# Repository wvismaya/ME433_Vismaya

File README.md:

Please refer the [Wiki here.](https://github.com/wvismaya/Northwestern_MSME_2k1617/wiki/Home)

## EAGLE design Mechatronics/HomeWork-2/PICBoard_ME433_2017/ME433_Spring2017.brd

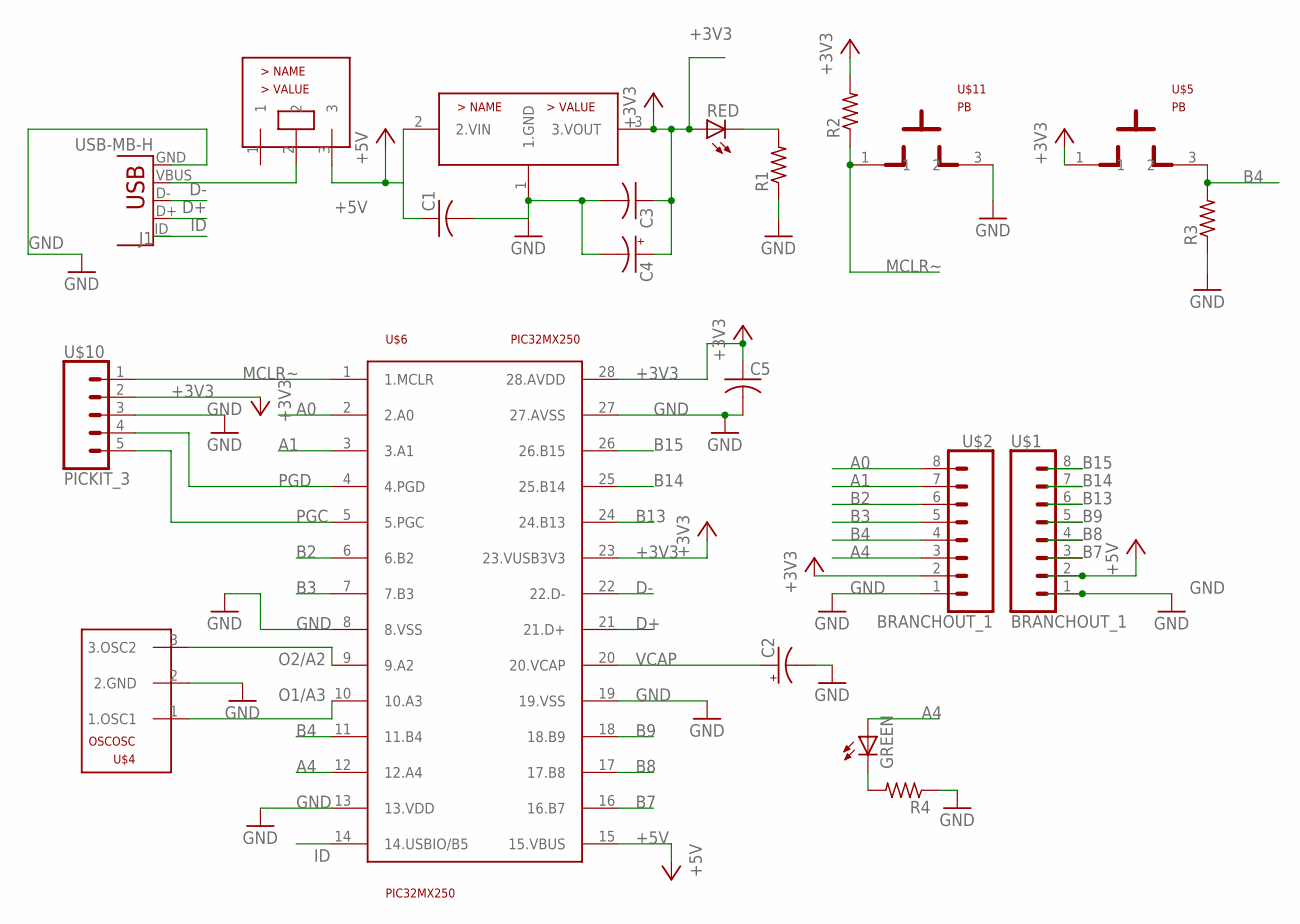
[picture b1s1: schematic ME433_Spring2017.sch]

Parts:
C1, C3, C5: C-US025-025X050; C025-025X050
C2, C4: CPOL-USB45181B; B45181B
GREEN: LED3MM
J1: USB-MB-H
R1, R2, R3, R4: R-US_0204/7; 0204/7
RED: LED3MM
U$1, U$2: BRANCHOUT_1; 1X08
U$4: OSCOSC; OSC
U$5, U$11: PB
U$6: PIC32MX250; DIL28-3
U$8: SLIDE
U$10: PICKIT_3; 1X05
_: MCP1702; TO92

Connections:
+3V3: C3.1, C4.+, C5.1, R2.2, RED.A, U$2.2, U$5.1, U$6.23 (23.VUSB3V3), U$6.28 (28.AVDD), U$10.2 (2.VDD), _.3 (3.VOUT)
+5V: C1.1, U$1.2, U$6.15 (15.VBUS), U$8.3, _.2 (2.VIN)
A0: U$2.8, U$6.2 (2.A0)
A1: U$2.7, U$6.3 (3.A1)
A4: GREEN.A, U$2.3, U$6.12 (12.A4)
B2: U$2.6, U$6.6 (6.B2)
B3: U$2.5, U$6.7 (7.B3)
B4: R3.2, U$2.4, U$5.3 (2), U$6.11 (11.B4)
B7: U$1.3, U$6.16 (16.B7)
B8: U$1.4, U$6.17 (17.B8)
B9: U$1.5, U$6.18 (18.B9)
B13: U$1.6, U$6.24 (24.B13)
B14: U$1.7, U$6.25 (25.B14)
B15: U$1.8, U$6.26 (26.B15)
D+: J1.D+, U$6.21 (21.D+)
D-: J1.D-, U$6.22 (22.D-)
GND: C1.2, C2.-, C3.2, C4.-, C5.2, J1.GND, R1.1, R3.1, R4.1, U$1.1, U$2.1, U$4.2 (2.GND), U$6.8 (8.VSS), U$6.13 (13.VDD), U$6.19 (19.VSS), U$6.27 (27.AVSS), U$10.3 (3.VSS), U$11.3 (2), _.1 (1.GND)
ID: J1.ID, U$6.14 (14.USBIO/B5)
MCLR~: R2.1, U$6.1 (1.MCLR), U$10.1 (1.MCLR~), U$11.1
unnamed: J1.VBUS, U$8.2
unnamed: R1.2, RED.K (C)
unnamed: GREEN.K (C), R4.2
O1/A3: U$4.1 (1.OSC1), U$6.10 (10.A3)
O2/A2: U$4.3 (3.OSC2), U$6.9 (9.A2)
PGC: U$6.5 (5.PGC), U$10.5 (5.PGC)
PGD: U$6.4 (4.PGD), U$10.4 (4.PGD)
VCAP: C2.+, U$6.20 (20.VCAP)

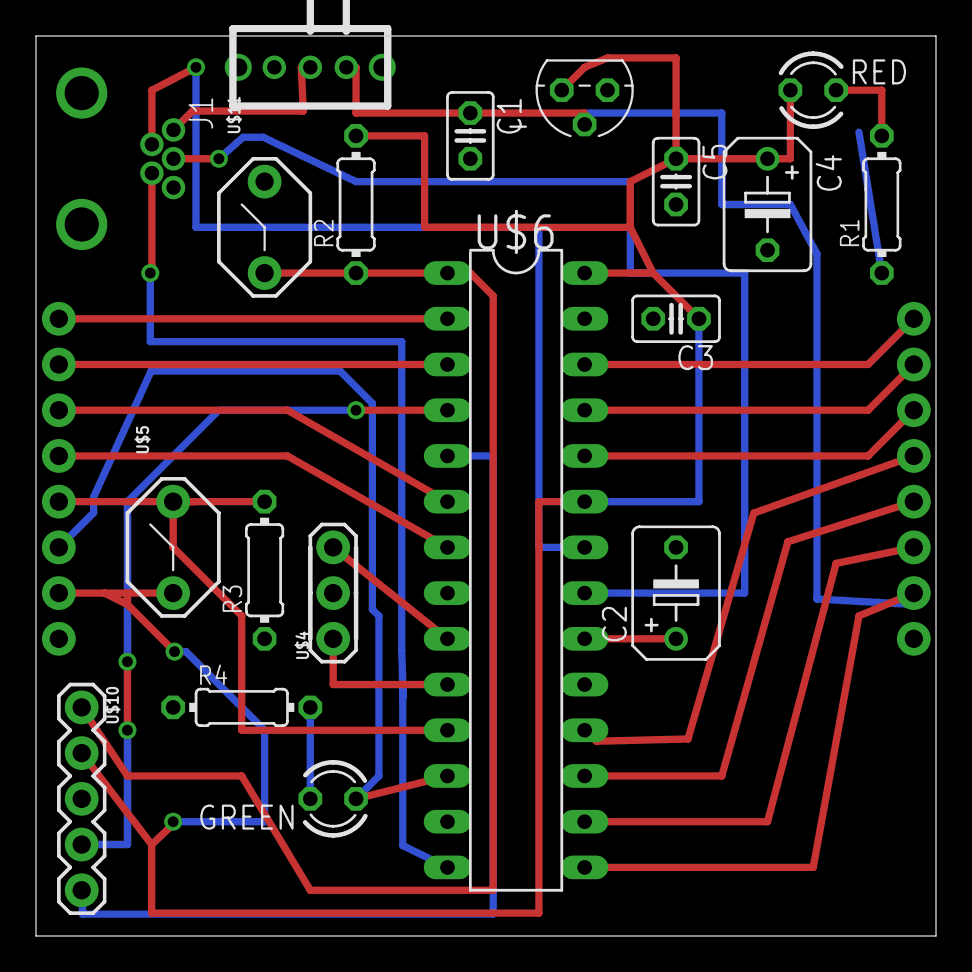
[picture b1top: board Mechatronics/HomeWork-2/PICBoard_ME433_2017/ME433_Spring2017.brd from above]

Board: 2 copper layers, 50.0 x 50.0 mm, 21 parts (0 on the bottom side), 27 nets.

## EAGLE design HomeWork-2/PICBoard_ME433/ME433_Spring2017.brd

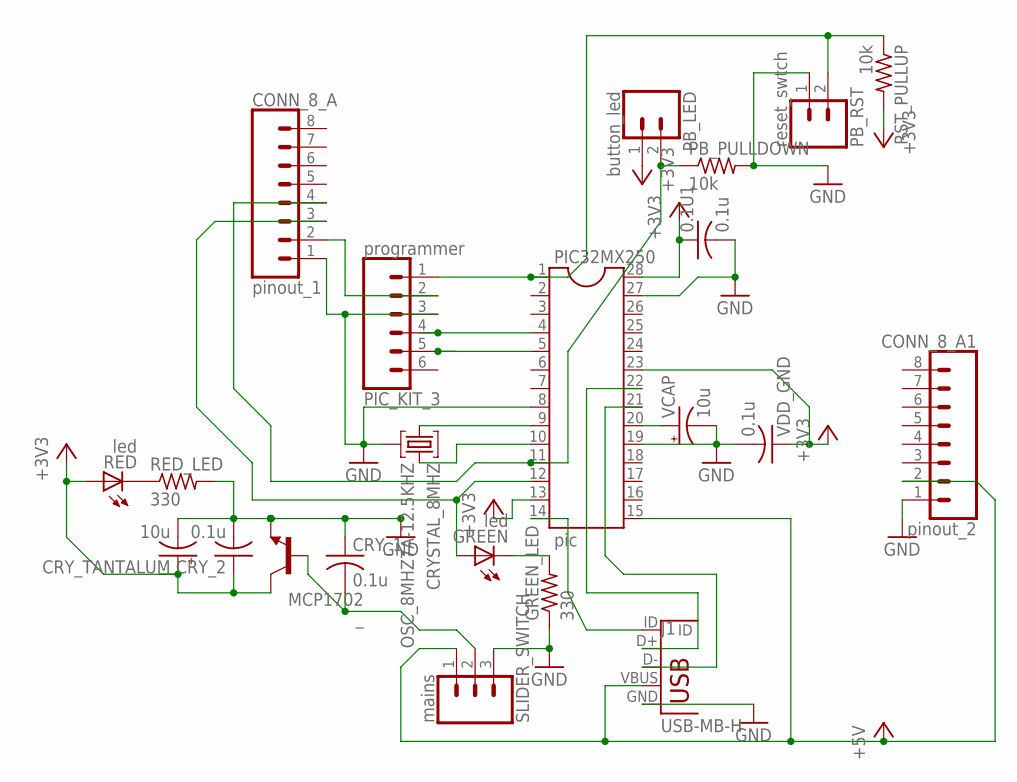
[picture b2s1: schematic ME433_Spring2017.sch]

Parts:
0.1U1: 0.1u; C025-025X050
CONN_8_A: pinout_1; 1X08
CONN_8_A1: pinout_2; 1X08
CRYSTAL_8MHZ: OSC_8MHZ7A-12.5KHZ; HC49U
CRY_1, CRY_2: 0.1u; C025-025X050
CRY_TANTALUM: 10u; B45181B
GREEN: led; SFH482
GREEN_LED: 330; 0204/7
J1: USB-MB-H
PB_LED: button_led; BUTTONS
PB_PULLDOWN: 10k; 0204/7
PB_RST: reset_swtch; BUTTONS
PIC32MX250: pic; PIC
PIC_KIT_3: programmer; 1X06_NO_SILK
RED: led; SFH482
RED_LED: 330; 0204/7
RST_PULLUP: 10k; 0204/7
SLIDER_SWITCH: mains; SLIDER_SWITCH_1MM
VCAP: 10u; B45181B
VDD_GND: 0.1u; C025-025X050
_: MCP1702

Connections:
+3V3: 0.1U1.1, CRY_2.1, CRY_TANTALUM.+, PB_LED.1, PIC32MX250.13, PIC32MX250.23, PIC32MX250.28, RED.A, RST_PULLUP.2, VDD_GND.1, _.C
+5V: CONN_8_A1.2, J1.VBUS, PIC32MX250.15, SLIDER_SWITCH.1
GND: 0.1U1.2, CONN_8_A.1, CONN_8_A1.1, CRYSTAL_8MHZ.2, CRY_1.1, CRY_2.2, CRY_TANTALUM.-, GREEN_LED.1, J1.GND, PB_PULLDOWN.2, PB_RST.1, PIC32MX250.8, PIC32MX250.19, PIC32MX250.27, PIC_KIT_3.3, RED_LED.2, SLIDER_SWITCH.3, VCAP.-, VDD_GND.2, _.E
unnamed: CONN_8_A.2, PIC_KIT_3.2
unnamed: PIC32MX250.4, PIC_KIT_3.4
unnamed: CONN_8_A.3, GREEN.A, PIC32MX250.12
unnamed: J1.D+, PIC32MX250.22
unnamed: CRYSTAL_8MHZ.1, PIC32MX250.9
unnamed: CRYSTAL_8MHZ.3, PIC32MX250.10
unnamed: GREEN.K (C), GREEN_LED.2
unnamed: PIC32MX250.5, PIC_KIT_3.5
unnamed: J1.D-, PIC32MX250.21
unnamed: CONN_8_A.4, PB_LED.2, PB_PULLDOWN.1, PIC32MX250.11
unnamed: PIC32MX250.20, VCAP.+
unnamed: CRY_1.2, SLIDER_SWITCH.2, _.B
unnamed: PB_RST.2, PIC32MX250.1, PIC_KIT_3.1, RST_PULLUP.1
unnamed: RED.K (C), RED_LED.1
unnamed: J1.ID, PIC32MX250.14

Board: 2 copper layers, 22 parts (1 on the bottom side), 18 nets, no tracks yet.

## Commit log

2017-03-30 Circuit Diagram of seemingly working prototype
2017-03-30 Uploaded without making a folder
2017-03-30 Upload of circuit diagram 1.1
2017-03-30 Screenshots of Clean-Unclean power supply
2017-03-30 Version1.1: Button=push-blinky
2017-03-30 1KHz Square wave
2017-03-30 Core Timer Added for Delays
2017-03-30 Macros Values perfected
2017-03-30 Circuit-Breadboard Snapshot
2017-03-30 Submission Ready
2017-04-02 Initialized new library
2017-04-02 Library Version #1; Initialize the Schematic
2017-04-02 Schematic Version #1
2017-04-02 Schematic Version #2
2017-04-04 Schematic Version #3 - Added PTH USB package
2017-04-04 Change in Schematic #1
2017-04-04 Final Layout #1
2017-04-05 Final Layout draft#2: Parse error for DRC
2017-04-07 Final Board
2017-04-07 Zip File: Submission Ready
2017-04-11 Update in main code
2017-04-11 Adding the Schematic: EAGLE
2017-04-11 Quick Reference picture of Schematic
2017-04-11 Main SPI code
2017-04-11 Display output
2017-04-11 SPI: Seperating Code into libraries
2017-04-11 Blinking LED: Seperating Code into libraries
2017-04-11 Blinking LED: Seperating Code into libraries: Update HW-1
2017-04-11 Update Main function with Library Links
2017-04-11 Rewrite Main with Libraries: Update HW-1
2017-04-13 I2C library
2017-04-13 Added Blinky
2017-04-13 Main file to blink LED on Expander
2017-04-13 Square Waves Generated
2017-04-18 Tested LCD
2017-04-18 Draws Lines of varying params
2017-04-18 Wrote H
2017-04-18 Wrote a string of arbitary characters
2017-04-18 Hello World !
2017-04-18 Added Slider
2017-04-19 Printed length counter on TFT screen
2017-04-19 Printed FPS: 37
2017-04-19 Submission Ready: Added Screenshot
2017-04-19 LCD with Expander: Working
2017-04-21 Changed PICKit 3 - Board working
2017-04-21 Got data from Gyro, Acc and Temp
2017-04-22 Variations in Acceleration
2017-04-22 Added Line clear function
2017-04-22 Commented Text values, added sliding bars
2017-04-22 Added Screenshot
2017-04-30 Paste IMU in Harmony: Submission Ready
2017-05-05 Homework 12 Submission Ready
2017-05-08 Send Device ID via USB
2017-05-08 Send IMU acceleration via USB
2017-05-10 Camera App with slider as sensitivity
2017-05-12 Colors a patch
2017-05-12 PIC end of Android-PIC comm
2017-05-12 Android end of Android-PIC communication
2017-05-18 Wheel 3D printing draft-1
2017-05-18 Wheel Print draft -1
2017-05-18 Wheel with Ridge
2017-05-18 Without Nozzle
2017-05-23 USB-HID travel straight
2017-06-01 laserCut the box
2017-06-01 DXF for lasercutting box
2017-06-01 Final Robot Wheels
2017-06-01 Revolve updated
2017-06-01 Wheel update in diameter -4.5
2017-06-01 Motor Mounts
2017-06-02 Chassis Draft 1
2017-06-02 chassis update
2017-06-02 Update mount
2017-06-02 Update wheel thickness
2017-06-02 phone_holder
2017-06-02 Halved in size
2017-06-02 Halved Size
2017-06-03 Final WHEEL!
2017-06-05 Enlongated Motor mounts
2017-06-05 Shortened and NO elongation
2017-06-06 Preliminary CAD Designs
2017-06-06 Screenshots of CAD
2017-06-06 Submission Ready - Printed Wheel
2017-06-06 Submission Ready - Laser Cut box
2017-06-07 phone holder
2017-06-07 smaller wheels
2017-06-07 thinner wheels
2017-06-07 Fillet - PIC holder
2017-06-07 androidholder
2017-06-09 Final Tech Cup Code
2017-06-09 rearrange design files: MainDesign
2017-06-09 Remove extra files
2017-06-09 Collect desgns in a folder
2018-01-31 Rearrange repo and add video
2018-01-31 Added all Northwestern Deliverable Code
2018-01-31 Added old / discarded projects
2018-02-05 Edit README to point to wiki
2018-02-05 Edited README to point to wiki
2018-02-05 Edited README to point to Wiki and Blakes repo
2018-02-05 Add reports for ME314 and ME454
